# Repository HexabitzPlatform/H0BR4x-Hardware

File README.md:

# H0BR41-Hardware
Hexabitz IMU &amp; Digital Compass Module Hardware Design

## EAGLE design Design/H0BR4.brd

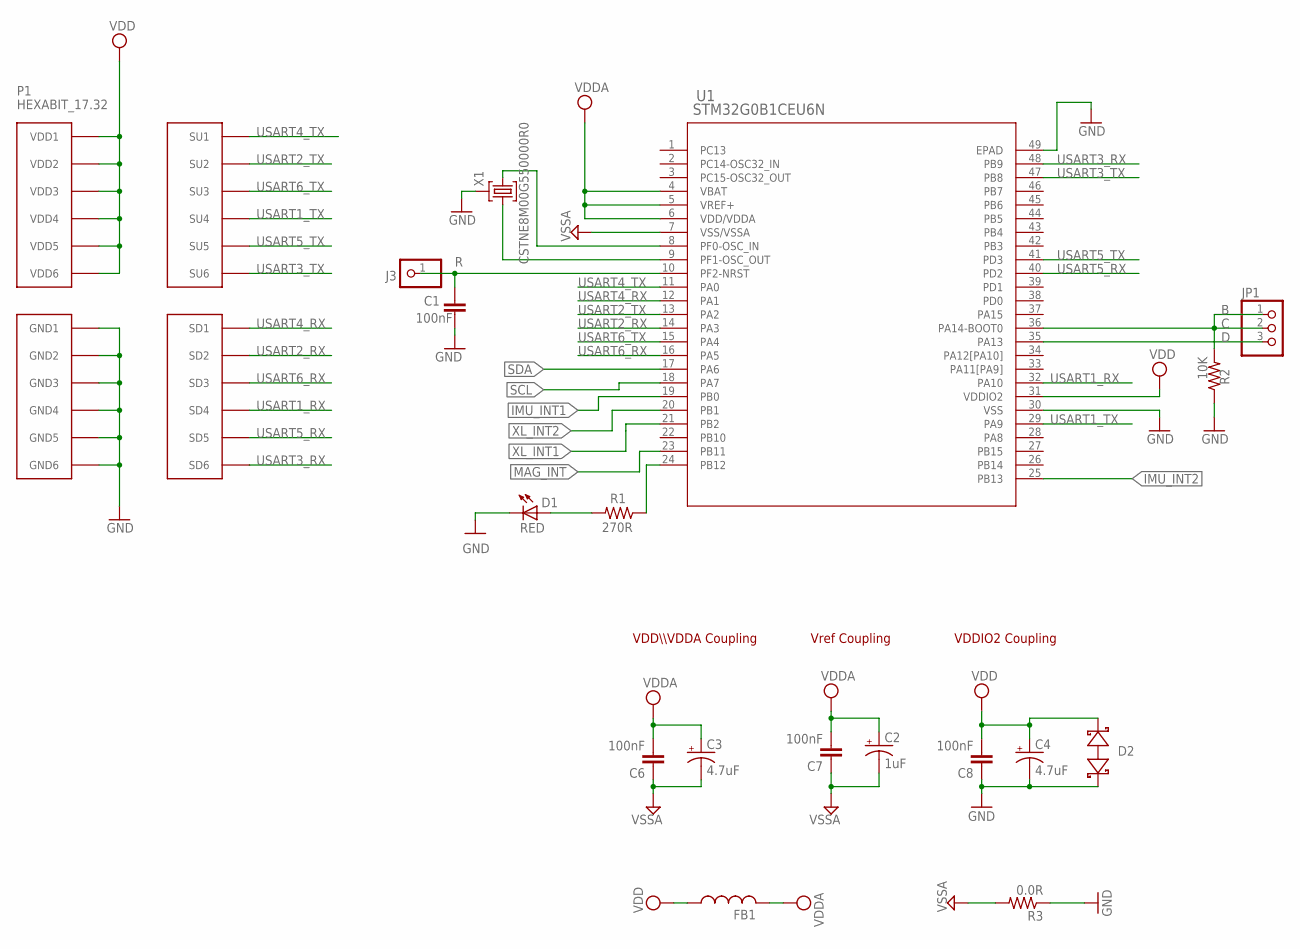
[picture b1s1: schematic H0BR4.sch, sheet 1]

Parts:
C1, C6, C7, C8: 100nF; C-0603; TOLERANCE 10%; VOLTAGE_RATING 16.0 V; MPN '0603YC104K4T2A
C2: 1uF; C-0805-POL; TOLERANCE 10%; VOLTAGE_RATING 16.0 V; MPN 'CC0805KKX7R7BB105
C3, C4: 4.7uF; C-0805-POL; TOLERANCE 20%; VOLTAGE_RATING 10.0 V; MPN 10TPU4R7MSI
D1: RED; VLMS1300-GS08
D2: BOURNS_CDSOD323-T03SCBOURNS_CDSOD323-T03SC_0_0; BOURNS_CDSOD323-T03SC_0
FB1: FB-TDK_MMZ1608Y300B; MPN MMZ1608Y300BTA00
J3: PINHD-1X1; 1X01
JP1: PINHD-1X3; 1X03
P1: HEXABIT_17.32
R1: 270R; R-0603; MPN 'ERJ-3GEYJ271V
R2: 10K; R-0603; MPN '060300J0103T5E
R3: 0.0R; R-0603; MPN RC0603JR-070RL
TRIMBLE-LOGO1: HEXA-LOGO
U1: STM32G0B1CEU6N; HEXABITZ_ICS_QFN_B1CEU6_STM-L
X1: CSTNE8M00G550000R0; XTALL_CSTCE8M00G52; MPN CSTNE8M00G550000R0

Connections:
C: JP1.1, JP1.2, R2.2, U1.36 (PA14-BOOT0)
D: JP1.3, U1.35 (PA13)
GND: C1.1, C4.2 (-), C8.1, D1.C, D2.1 (A), P1.PAD_PD7 (GND1), P1.PAD_PD8 (GND2), P1.PAD_PD9 (GND3), P1.PAD_PD10 (GND4), P1.PAD_PD11 (GND5), P1.PAD_PD12 (GND6), R2.1, R3.1, U1.30 (VSS), U1.49 (EPAD), X1.P$2 (2); also elsewhere on the board
GND1: C2.2 (-), C3.2 (-), C6.1, C7.1, R3.2, U1.7 (VSS/VSSA)
IMU_INT1: U1.19 (PB0); also elsewhere on the board
IMU_INT2: U1.25 (PB13); also elsewhere on the board
MAG_INT: U1.23 (PB11); also elsewhere on the board
unnamed: R1.1, U1.24 (PB12)
unnamed: U1.9 (PF1-OSC_OUT), X1.P$3 (3)
unnamed: D1.A, R1.2
unnamed: U1.8 (PF0-OSC_IN), X1.P$1 (1)
R: C1.2, J3.1, U1.10 (PF2-NRST)
SCL: U1.18 (PA7); also elsewhere on the board
SDA: U1.17 (PA6); also elsewhere on the board
USART1_RX: P1.PAD_PD4 (SD4), U1.32 (PA10)
USART1_TX: P1.PAD_PU4 (SU4), U1.29 (PA9)
USART2_RX: P1.PAD_PD2 (SD2), U1.14 (PA3)
USART2_TX: P1.PAD_PU2 (SU2), U1.13 (PA2)
USART3_RX: P1.PAD_PD6 (SD6), U1.48 (PB9)
USART3_TX: P1.PAD_PU6 (SU6), U1.47 (PB8)
USART4_RX: P1.PAD_PD1 (SD1), U1.12 (PA1)
USART4_TX: P1.PAD_PU1 (SU1), U1.11 (PA0)
USART5_RX: P1.PAD_PD5 (SD5), U1.40 (PD2)
USART5_TX: P1.PAD_PU5 (SU5), U1.41 (PD3)
USART6_RX: P1.PAD_PD3 (SD3), U1.16 (PA5)
USART6_TX: P1.PAD_PU3 (SU3), U1.15 (PA4)
VCC: C2.1 (+), C3.1 (+), C6.2, C7.2, FB1.2, U1.4 (VBAT), U1.5 (VREF+), U1.6 (VDD/VDDA)
VDD: C4.1 (+), C8.2, D2.2 (C), FB1.1, P1.PAD_PU7 (VDD1), P1.PAD_PU8 (VDD2), P1.PAD_PU9 (VDD3), P1.PAD_PU10 (VDD4), P1.PAD_PU11 (VDD5), P1.PAD_PU12 (VDD6), U1.31 (VDDIO2); also elsewhere on the board
XL_INT1: U1.21 (PB2); also elsewhere on the board
XL_INT2: U1.20 (PB1); also elsewhere on the board

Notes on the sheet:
VDDIO2 Coupling
VDD\\\VDDA Coupling
Vref Coupling

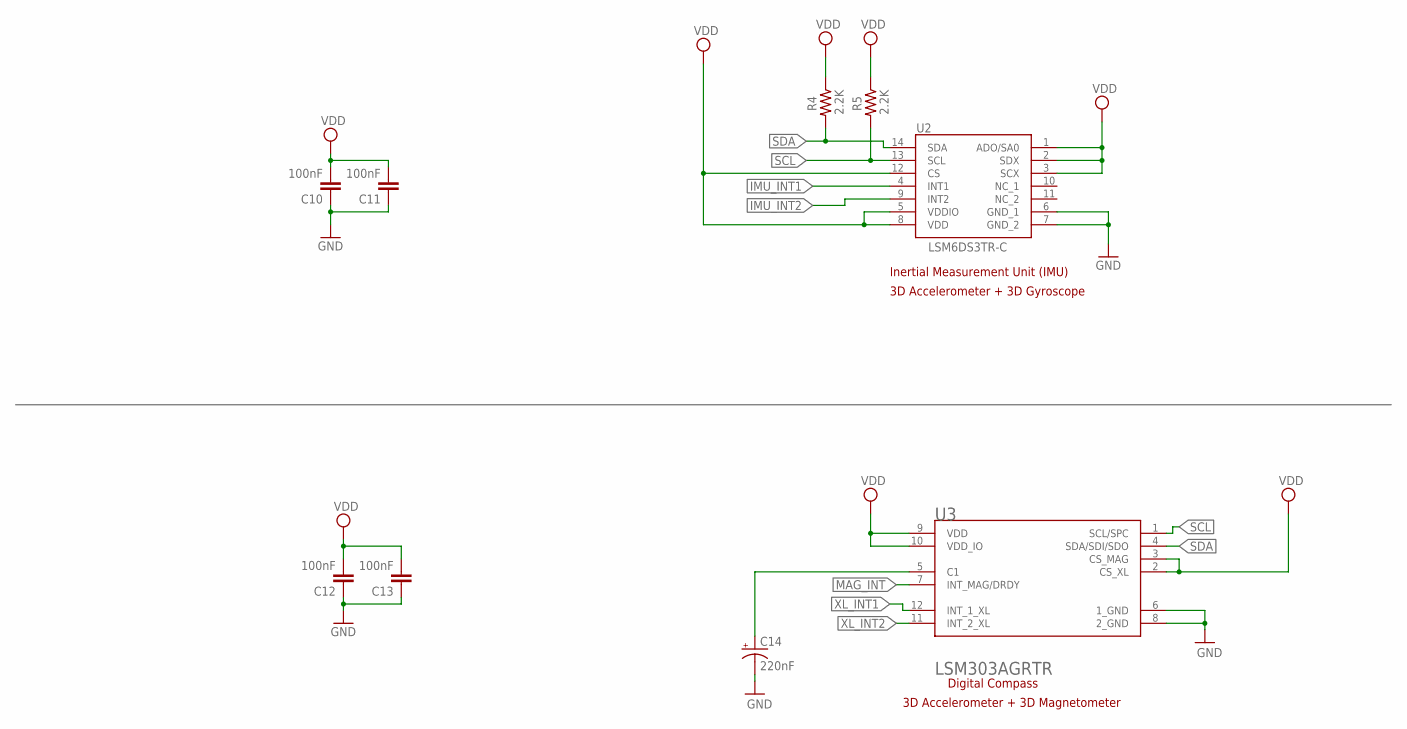
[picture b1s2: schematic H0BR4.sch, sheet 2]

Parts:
C10, C11, C12, C13: 100nF; C-0603; TOLERANCE 10%; VOLTAGE_RATING 16.0 V; MPN '0603YC104K4T2A
C14: 220nF; C-0805-POL; TOLERANCE 20%; VOLTAGE_RATING 10.0 V; MPN C0805C224K1RACTU
R4, R5: 2.2K; R-0603; TOLERANCE 5%; MPN RC0603FR-072K2L
U2: LSM6DS3TR-C; LGA-14(2.5X3X0.86)
U3: STMICROELECTRONICS_LSM303AGRTRSTMICROELECTRONICS_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; STMICROELECTRONICS_LSM303AGRTR_0

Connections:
GND: C10.1, C11.1, C12.1, C13.1, C14.2 (-), U2.6 (GND_1), U2.7 (GND_2), U3.6 (1_GND), U3.8 (2_GND); also elsewhere on the board
IMU_INT1: U2.4 (INT1); also elsewhere on the board
IMU_INT2: U2.9 (INT2); also elsewhere on the board
MAG_INT: U3.7 (INT_MAG/DRDY); also elsewhere on the board
unnamed: C14.1 (+), U3.5 (C1)
SCL: R5.2, U2.13 (SCL), U3.1 (SCL/SPC); also elsewhere on the board
SDA: R4.2, U2.14 (SDA), U3.4 (SDA/SDI/SDO); also elsewhere on the board
VDD: C10.2, C11.2, C12.2, C13.2, R4.1, R5.1, U2.1 (ADO/SA0), U2.2 (SDX), U2.3 (SCX), U2.5 (VDDIO), U2.8 (VDD), U2.12 (CS), U3.2 (CS_XL), U3.3 (CS_MAG), U3.9 (VDD), U3.10 (VDD_IO); also elsewhere on the board
XL_INT1: U3.12 (INT_1_XL); also elsewhere on the board
XL_INT2: U3.11 (INT_2_XL); also elsewhere on the board

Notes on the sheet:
Inertial Measurement Unit (IMU)
3D Accelerometer + 3D Gyroscope
Digital Compass
3D Accelerometer + 3D Magnetometer

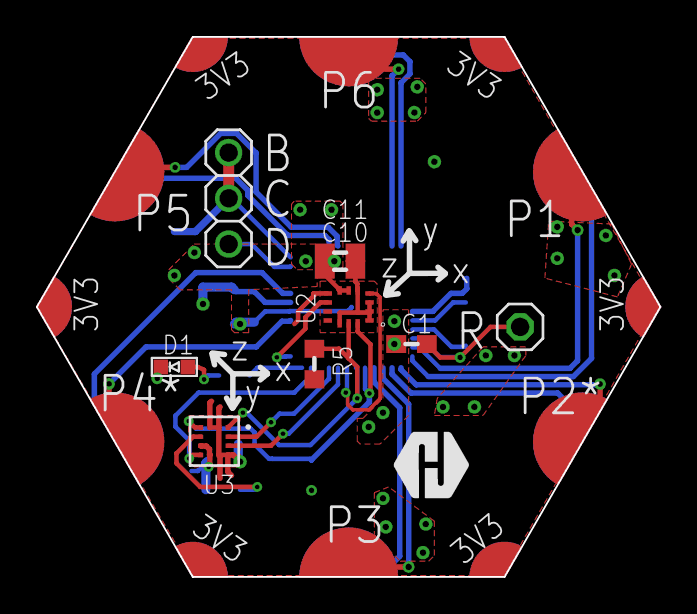
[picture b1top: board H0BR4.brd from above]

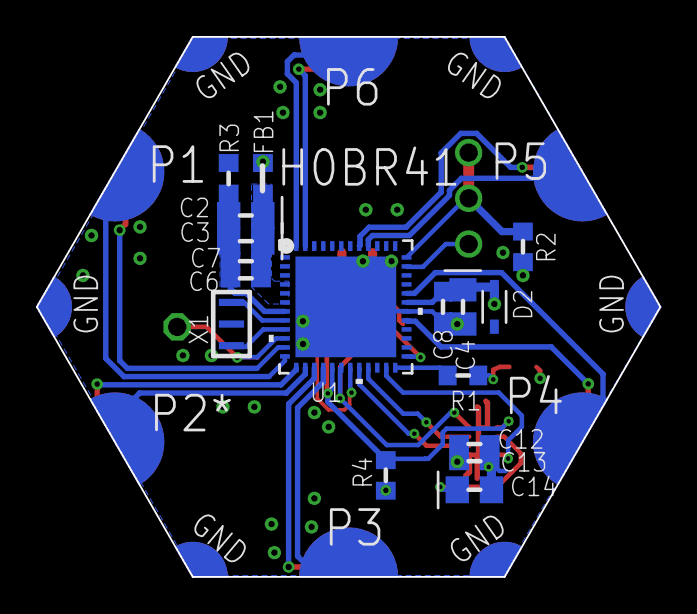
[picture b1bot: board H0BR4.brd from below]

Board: 2 copper layers, 34.6 x 30.0 mm, 28 parts (17 on the bottom side), 31 nets.

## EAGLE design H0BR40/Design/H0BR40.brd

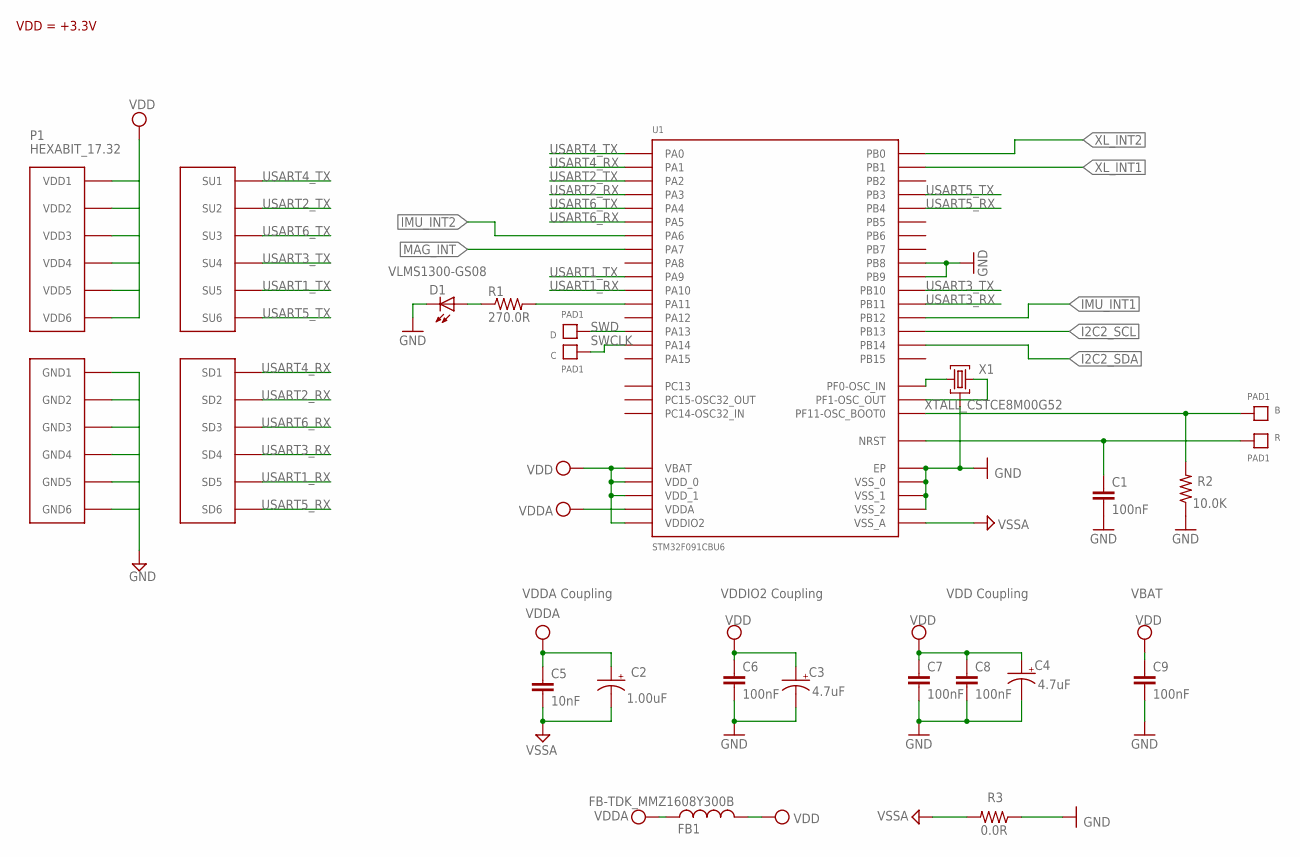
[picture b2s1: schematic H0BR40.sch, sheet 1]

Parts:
B: PAD1
C: PAD1
C1, C6, C7, C8: 100nF; C-0603; TOLERANCE 10%; VOLTAGE_RATING 16.0 V; MPN 0603YC104K4T2A
C2: 1.00uF; C-0805-POL; TOLERANCE 10%; VOLTAGE_RATING 16.0 V; MPN TAJR105M016RNJ
C3: 4.7uF; C-0805-POL; TOLERANCE 20%; VOLTAGE_RATING 10.0 V; MPN 10TPU4R7MSI
C4: 4.7uF; C-0805-POL; TOLERANCE 10%; VOLTAGE_RATING 10 V; MPN 10TPU4R7MSI
C5: 10nF; C-0603; TOLERANCE 10%; VOLTAGE_RATING 16.0 V; MPN 0603YC103KAT4A
C9: 100nF; C-0603; TOLERANCE 16.0 V; VOLTAGE_RATING 10%; MPN 0603YC104K4T2A
D: PAD1
D1: VLMS1300-GS08; MPN VLMS1300-GS08
FB1: FB-TDK_MMZ1608Y300B; MPN MMZ1608Y300B
P1: HEXABIT_17.32
R: PAD1
R1: 270.0R; R-0603; TOLERANCE 5%; MPN ERJ-3GEYJ271V
R2: 10.0K; R-0603; TOLERANCE 5%; MPN CRCW060310K0JNEB
R3: 0.0R; R-0603; MPN CRCW06030000Z0EAHP
U1: STM32F091CBU6
X1: XTALL_CSTCE8M00G52

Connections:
B1: B.P$1, B.P$2, R2.2, U1.P$44 (PF11-OSC_BOOT0)
GND: C1.2, C3.2 (-), C4.2 (-), C6.2, C7.2, C8.2, C9.2, D1.C, P1.PAD_PD7 (GND1), P1.PAD_PD8 (GND2), P1.PAD_PD9 (GND3), P1.PAD_PD10 (GND4), P1.PAD_PD11 (GND5), P1.PAD_PD12 (GND6), R2.1, R3.1, U1.EP, U1.P$23 (VSS_0), U1.P$35 (VSS_1), U1.P$45 (PB8), U1.P$46 (PB9), U1.P$47 (VSS_2), X1.P$2 (2); also elsewhere on the board
I2C2_SCL: U1.P$26 (PB13); also elsewhere on the board
I2C2_SDA: U1.P$27 (PB14); also elsewhere on the board
IMU_INT1: U1.P$25 (PB12); also elsewhere on the board
IMU_INT2: U1.P$16 (PA6); also elsewhere on the board
MAG_INT: U1.P$17 (PA7); also elsewhere on the board
unnamed: R1.2, U1.P$32 (PA11)
unnamed: D1.A, R1.1
unnamed: U1.P$5 (PF0-OSC_IN), X1.P$1 (1)
unnamed: U1.P$6 (PF1-OSC_OUT), X1.P$3 (3)
R1: C1.1, R.P$1, R.P$2, U1.P$7 (NRST)
SWCLK: C.P$1, C.P$2, U1.P$37 (PA14)
SWD: D.P$1, D.P$2, U1.P$34 (PA13)
USART1_RX: P1.PAD_PD5 (SD5), U1.P$31 (PA10)
USART1_TX: P1.PAD_PU5 (SU5), U1.P$30 (PA9)
USART2_RX: P1.PAD_PD2 (SD2), U1.P$13 (PA3)
USART2_TX: P1.PAD_PU2 (SU2), U1.P$12 (PA2)
USART3_RX: P1.PAD_PD4 (SD4), U1.P$22 (PB11)
USART3_TX: P1.PAD_PU4 (SU4), U1.P$21 (PB10)
USART4_RX: P1.PAD_PD1 (SD1), U1.P$11 (PA1)
USART4_TX: P1.PAD_PU1 (SU1), U1.P$10 (PA0)
USART5_RX: P1.PAD_PD6 (SD6), U1.P$40 (PB4)
USART5_TX: P1.PAD_PU6 (SU6), U1.P$39 (PB3)
USART6_RX: P1.PAD_PD3 (SD3), U1.P$15 (PA5)
USART6_TX: P1.PAD_PU3 (SU3), U1.P$14 (PA4)
VDD: C3.1 (+), C4.1 (+), C6.1, C7.1, C8.1, C9.1, FB1.2, P1.PAD_PU7 (VDD1), P1.PAD_PU8 (VDD2), P1.PAD_PU9 (VDD3), P1.PAD_PU10 (VDD4), P1.PAD_PU11 (VDD5), P1.PAD_PU12 (VDD6), U1.P$1 (VBAT), U1.P$24 (VDD_0), U1.P$36 (VDDIO2), U1.P$48 (VDD_1); also elsewhere on the board
VDDA: C2.1 (+), C5.1, FB1.1, U1.P$9 (VDDA)
VSSA: C2.2 (-), C5.2, R3.2, U1.P$8 (VSS_A)
XL_INT1: U1.P$19 (PB1); also elsewhere on the board
XL_INT2: U1.P$18 (PB0); also elsewhere on the board

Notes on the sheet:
VDDA Coupling
VDDIO2 Coupling
VDD Coupling
VBAT
VDD = +3.3V

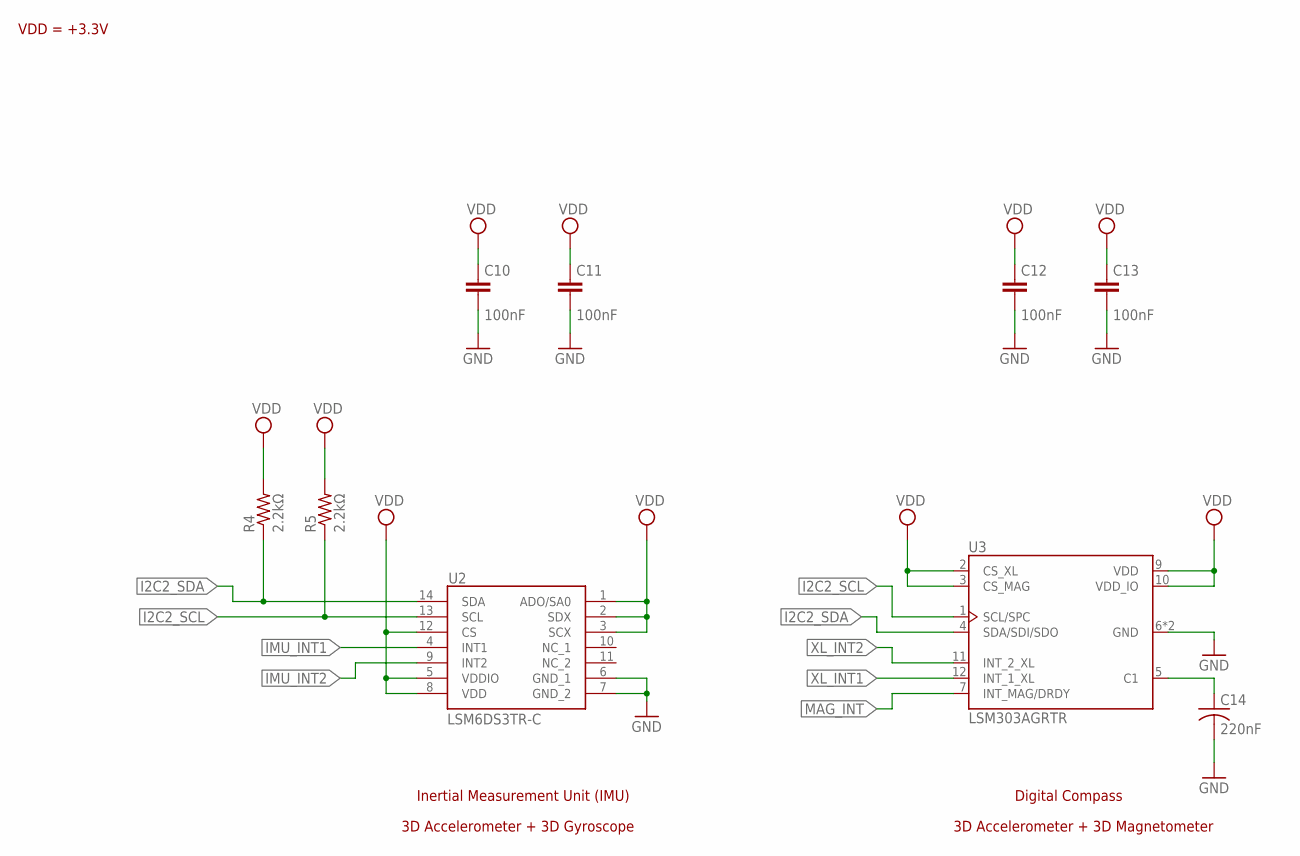
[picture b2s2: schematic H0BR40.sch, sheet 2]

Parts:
C10, C11, C12, C13: 100nF; C-0603; TOLERANCE ±10%; VOLTAGE_RATING 16.0V; MPN 0603YC104K4T2A
C14: 220nF; C-0805; TOLERANCE ±10%; VOLTAGE_RATING 100.0V; MPN C0805C224K1RACTU
R4, R5: 2.2kΩ; R-0603; TOLERANCE ±1%; MPN CRCW06032K20FKEA
U2: LSM6DS3TR-C; LGA-14(2.5X3X0.86)
U3: LSM303AGRTR; LGA12R50P_200X200X100

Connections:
GND: C10.2, C11.2, C12.2, C13.2, C14.2, U2.6 (GND_1), U2.7 (GND_2), U3.6 (GND), U3.8 (GND); also elsewhere on the board
I2C2_SCL: R5.1, U2.13 (SCL), U3.1 (SCL/SPC); also elsewhere on the board
I2C2_SDA: R4.1, U2.14 (SDA), U3.4 (SDA/SDI/SDO); also elsewhere on the board
IMU_INT1: U2.4 (INT1); also elsewhere on the board
IMU_INT2: U2.9 (INT2); also elsewhere on the board
MAG_INT: U3.7 (INT_MAG/DRDY); also elsewhere on the board
unnamed: C14.1, U3.5 (C1)
VDD: C10.1, C11.1, C12.1, C13.1, R4.2, R5.2, U2.1 (ADO/SA0), U2.2 (SDX), U2.3 (SCX), U2.5 (VDDIO), U2.8 (VDD), U2.12 (CS), U3.2 (CS_XL), U3.3 (CS_MAG), U3.9 (VDD), U3.10 (VDD_IO); also elsewhere on the board
XL_INT1: U3.12 (INT_1_XL); also elsewhere on the board
XL_INT2: U3.11 (INT_2_XL); also elsewhere on the board

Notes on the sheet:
Inertial Measurement Unit (IMU)
3D Accelerometer + 3D Gyroscope
Digital Compass
3D Accelerometer + 3D Magnetometer
VDD = +3.3V

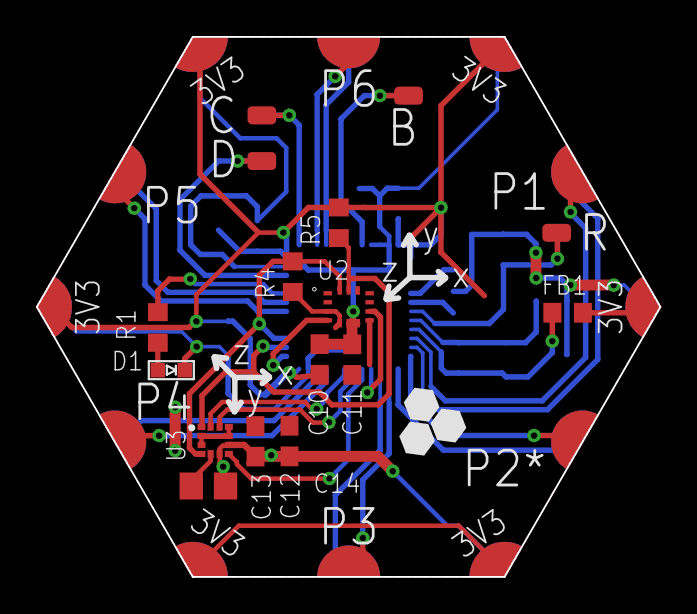
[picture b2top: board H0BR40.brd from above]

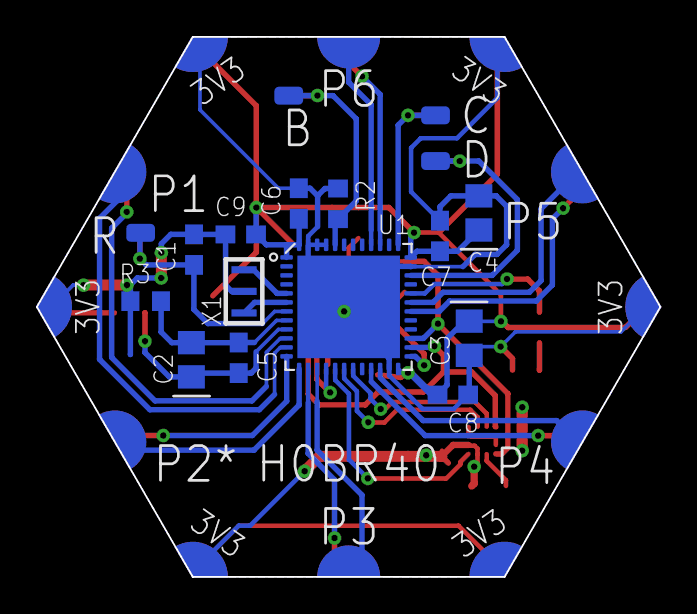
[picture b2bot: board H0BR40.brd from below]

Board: 2 copper layers, 34.6 x 30.0 mm, 30 parts (13 on the bottom side), 32 nets.

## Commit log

2019-05-23 First release rev 0
2020-03-11 in this commit: - renamed all res and caps to match circuitmaker original design - fixed BOM files (note: in circuit maker and website C15 should be C14) - regenerated documentation and all output fi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
2022-08-23 Changing the MC to STM32G0B1CEU6N
2022-08-23 Changing the MC to STM32G0B1CEU6
2022-09-13 -Changing the layout to be like of master design in terms of the position of sensors ICs . -Changing the Schematic as well
2022-09-13 -Correcting some fault connections
2022-10-30 -Correcting some issues related to part names
2024-02-15 -Improving the layout
2024-02-24 -Fix documentaion issue
2024-04-17 update the logo add TVS
2024-04-17 Fix silkscreen issue
2024-05-16 -Standrize the folders arranging -Remove C9 from the BOM

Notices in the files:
parts and their libraries:
HEXABITZ_ICs: COPYRIGHT: Copyright (C) 2022 Ultra Librarian. All rights reserved.
